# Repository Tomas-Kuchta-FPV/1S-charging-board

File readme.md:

# 1S charging board
> A compact adapter board that lets standard RC chargers safely charge 1S batteries.

It allows you to charge up to six 1s batteries on a universal RC charger.  
Some chargers can display series resistance and capacity. So you know the conditions of the cells.  
Connectors like **BT2.0/A30** and **XT30** are suported. And with an adapter, you can charge **18650** batteries.  

## Photos
### Main PCB

### XT30 to 18650

## Motivation
I have a great RC charger (ISDT D1), and it measures internal resistance and capacity, which is awesome!  
There are a lot of 18650 cells of unknown condition lying in my workshop. I would like to know if they are still good or if they belong in the trash.  
Also, I love RC hobby. So why not use a universal both RC charger for RC and maker stuff?  
That's why there is a main PCB with XT30 and BT 2.0 connectors. And an extension board for 18650.

### Design constraints
- It should work with these battery types and connctors:
    - Modular design with BT2.0 on top and XT30 on the sides for modules.
    - XT30 - Main board
    - BT2.0 / A30 Main board
    - PH2.0 - future adapters if I need them
    - 18650 batteries - XT30 to 18650
- easy to use
- A fuse - 2A Polyfuze
- 6S MAX

## BOM
| Item                       | Qty | Price | Link                                                  |
| :------------------------- | :-- | :---- | :---------------------------------------------------- |
|                            |     |       |                                                       |
| BT2.0M                     | 6   | 7.15  | https://www.aliexpress.com/item/1005004465425088.html |
| 2A Polyfuse                | 1   | 0.51  | https://www.lcsc.com/product-detail/C960026.html      |
| XT60 - Power Input         | 1   | 0.59  | https://www.lcsc.com/product-detail/C98732.html       |
| 1x7P -  Balance input      | 1   | 0.54  | https://www.lcsc.com/product-detail/C144398.html      |
| 2x07 PinHeader             | 1   | 1.4   | https://www.lcsc.com/product-detail/C2897408.html     |
| XT30M                      | 6   | 1.72  | https://www.lcsc.com/product-detail/C431092.html      |
|                            |     |       |                                                       |
| XT30F                      | 6   | 1.92  | https://www.lcsc.com/product-detail/C2913282.html     |
| 18650 holder               | 6   | 7.52  | https://www.lcsc.com/product-detail/C2988620.html     |
| LCSC Shipping              |     | 11.2  |                                                       |
| PCB fabrication + shipping | 2   | 21.9  |                                                       |
|                            |     | 54.45 |                                                       |

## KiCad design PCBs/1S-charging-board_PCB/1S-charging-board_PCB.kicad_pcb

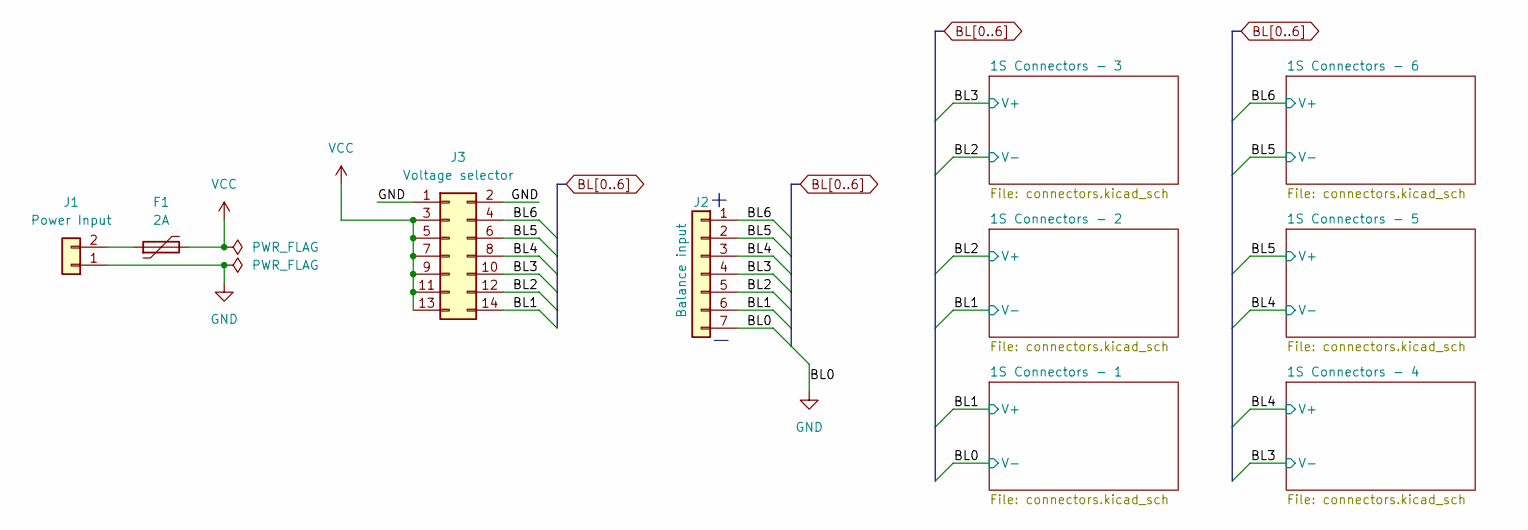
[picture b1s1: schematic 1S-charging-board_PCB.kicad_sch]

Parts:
F1: 2A; Fuse_1812_4532Metric_Pad1.30x3.40mm_HandSolder; LCSC C960026
J1: Power Input; AMASS_XT60PW-M_1x02_P7.20mm_Horizontal; LCSC C98732
J2: Balance input; JST_XH_B7B-XH-A_1x07_P2.50mm_Vertical; LCSC C144398
J3: Voltage selector; PinHeader_2x07_P2.54mm_Vertical; LCSC C2897408

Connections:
BL1: J2.6, J3.14; also elsewhere on the board
BL2: J2.5, J3.12; also elsewhere on the board
BL3: J2.4, J3.10; also elsewhere on the board
BL4: J2.3, J3.8; also elsewhere on the board
BL5: J2.2, J3.6; also elsewhere on the board
BL6: J2.1, J3.4; also elsewhere on the board
GND: J1.1, J2.7, J3.1, J3.2; also elsewhere on the board
unnamed: F1.1, J1.2
VCC: F1.2, J3.3, J3.5, J3.7, J3.9, J3.11, J3.13

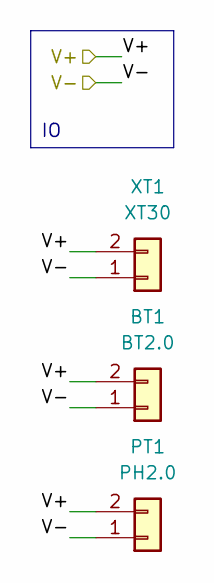
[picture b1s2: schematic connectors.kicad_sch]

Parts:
BT1: BT2.0; BT20
PT1: PH2.0; JST_PH_B2B-PH-K_1x02_P2.00mm_Vertical; LCSC C131337
XT1: XT30; AMASS_XT30PW-M_1x02_P2.50mm_Horizontal; LCSC C431092

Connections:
BL1: BT1.2, XT1.2; also elsewhere on the board
GND: BT1.1, XT1.1; also elsewhere on the board

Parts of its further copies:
BT2, BT3, BT4, BT5, BT6: BT2.0; BT20
XT2, XT3, XT4, XT5, XT6: XT30; AMASS_XT30PW-M_1x02_P2.50mm_Horizontal; LCSC C431092

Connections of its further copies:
BL1: BT2.1, XT2.1; also elsewhere on the board
BL2: BT2.2, BT3.1, XT2.2, XT3.1; also elsewhere on the board
BL3: BT3.2, BT4.1, XT3.2, XT4.1; also elsewhere on the board
BL4: BT4.2, BT5.1, XT4.2, XT5.1; also elsewhere on the board
BL5: BT5.2, BT6.1, XT5.2, XT6.1; also elsewhere on the board
BL6: BT6.2, XT6.2; also elsewhere on the board

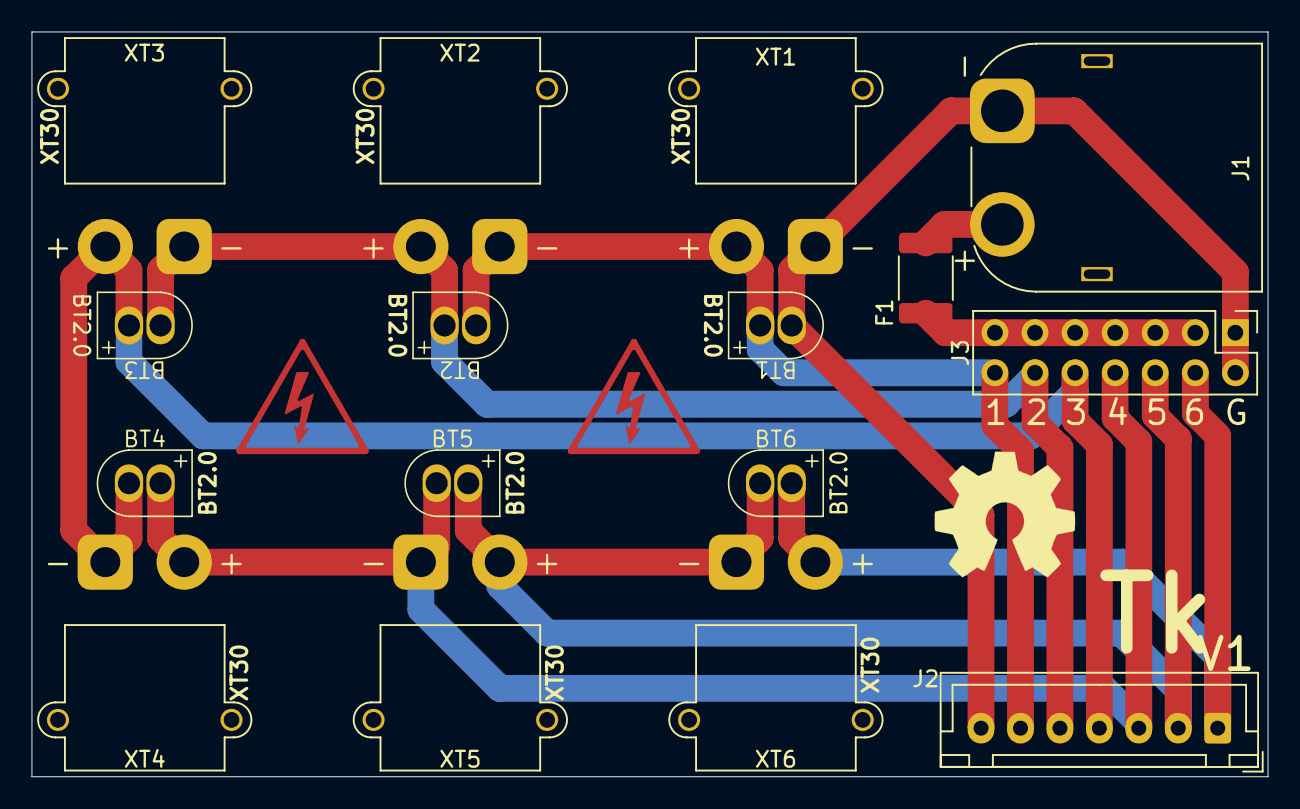
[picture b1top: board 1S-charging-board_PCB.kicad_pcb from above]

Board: 2 copper layers, 78.3 x 47.2 mm, 16 parts (0 on the bottom side), 9 nets.

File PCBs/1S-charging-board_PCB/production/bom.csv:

Designator,Footprint,Quantity,Value,LCSC Part #
"BT1, BT2, BT3, BT4, BT5, BT6",BT20,6,BT2.0,-
F1,1812,1,2A,C960026
J1,AMASS_XT60PW-M_1x02_P7.20mm_Horizontal,1,Power Input,C98732
J2,JST_XH_B7B-XH-A_1x07_P2.50mm_Vertical,1,Balance input,C144398
J3,PinHeader_2x07_P2.54mm_Vertical,1,Voltage selector,C2897408
"XT1, XT2, XT3, XT4, XT5, XT6",AMASS_XT30PW-M_1x02_P2.50mm_Horizontal,6,XT30,C431092

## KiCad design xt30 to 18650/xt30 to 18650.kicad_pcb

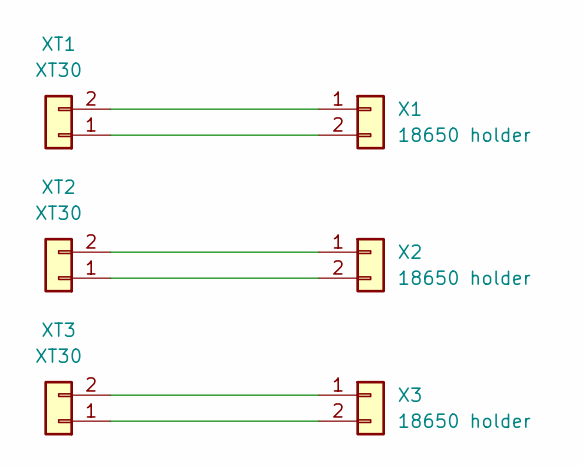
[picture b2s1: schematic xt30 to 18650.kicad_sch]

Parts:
X1, X2, X3: 18650 holder; BatteryHolder_Keystone_1042_1x18650; LCSC C2988620
XT1, XT2, XT3: XT30; AMASS_XT30PW-F_1x02_P2.50mm_Horizontal; LCSC C2913282

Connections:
unnamed: X1.1, XT1.2
unnamed: X1.2, XT1.1
unnamed: X2.1, XT2.2
unnamed: X2.2, XT2.1
unnamed: X3.1, XT3.2
unnamed: X3.2, XT3.1

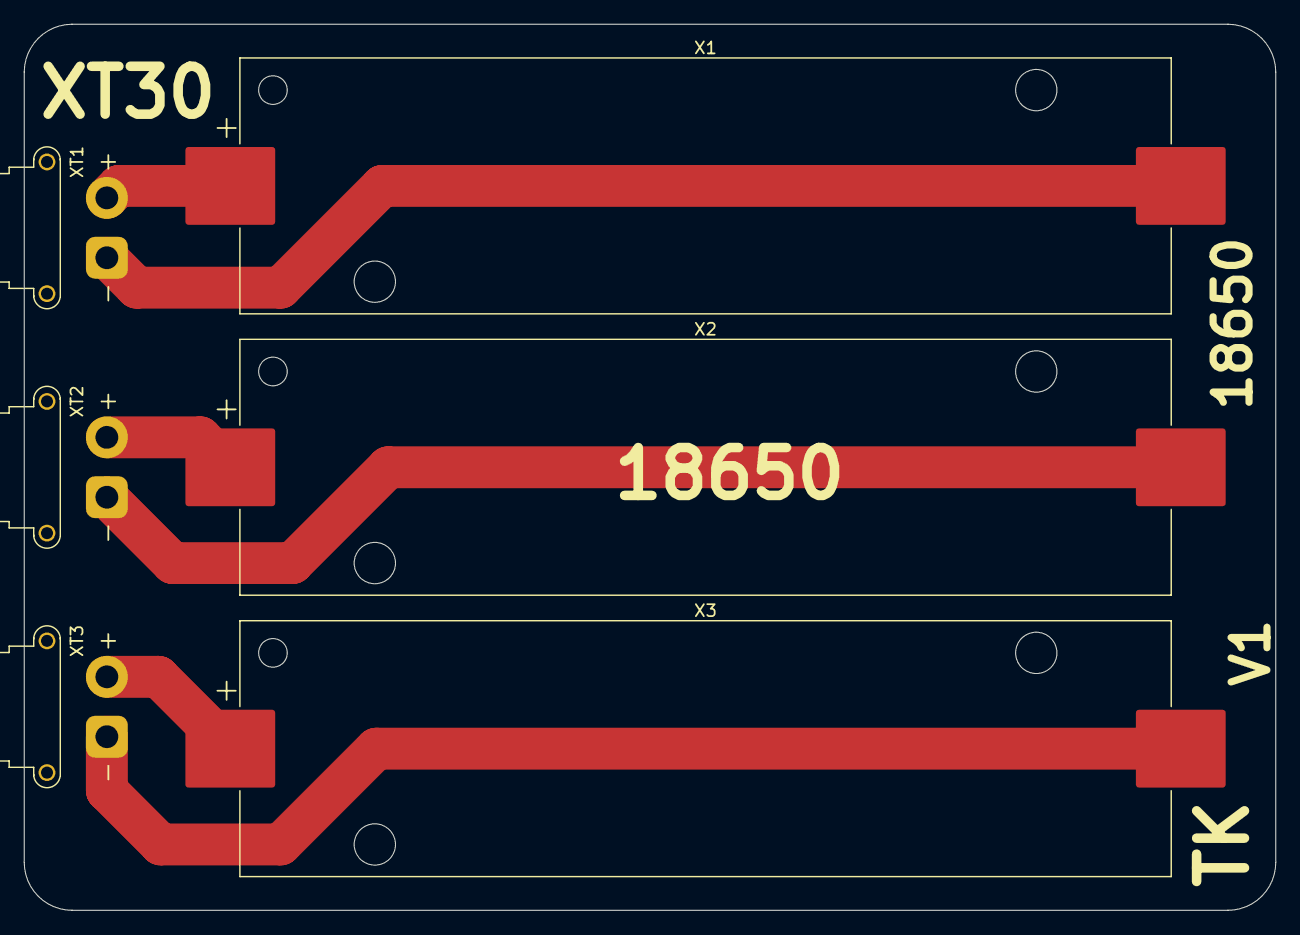
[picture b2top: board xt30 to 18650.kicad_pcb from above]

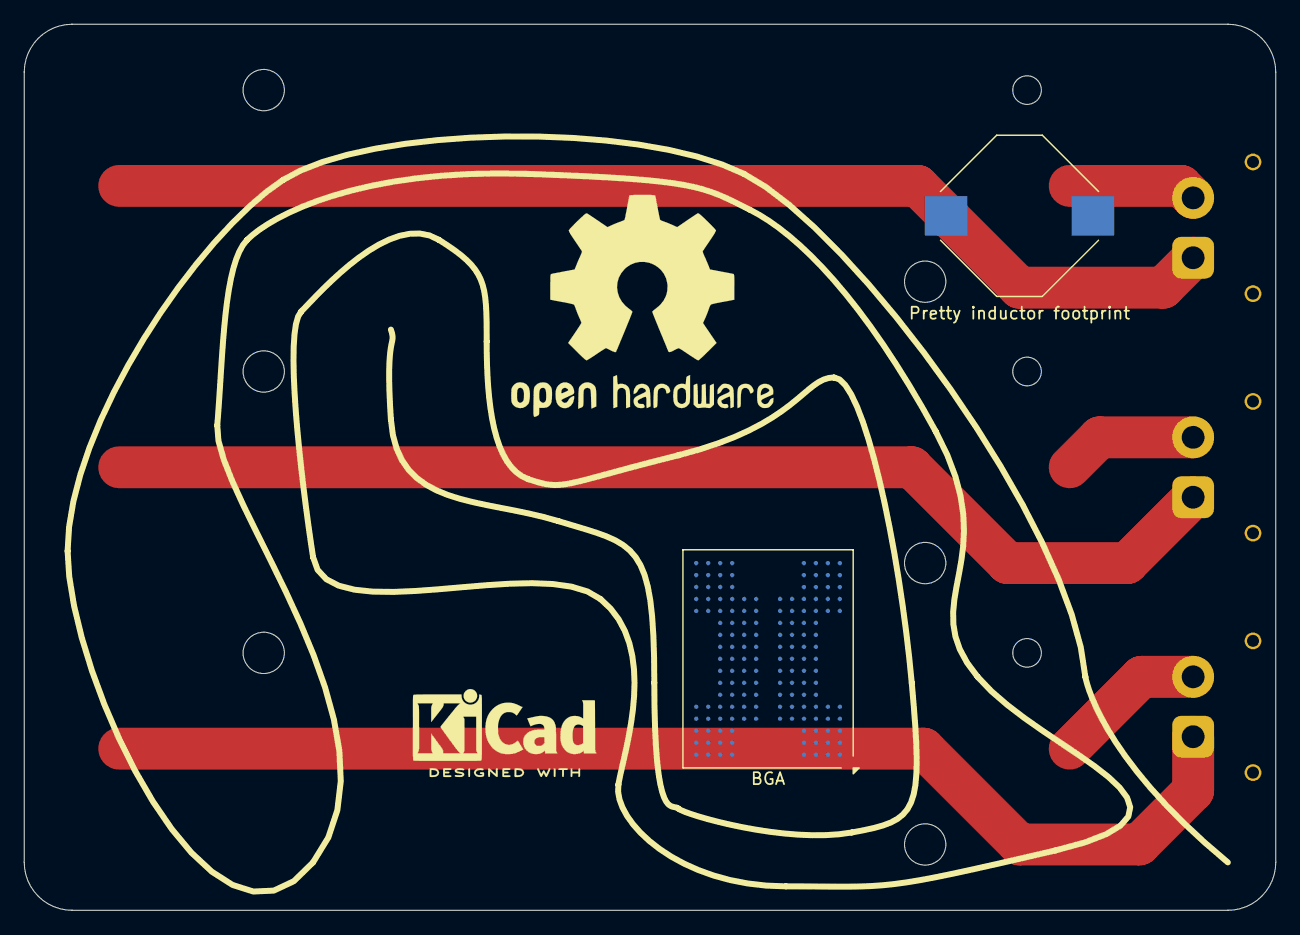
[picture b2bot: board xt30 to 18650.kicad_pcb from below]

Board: 2 copper layers, 104.5 x 74.0 mm, 8 parts (2 on the bottom side), 6 nets.

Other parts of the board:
BGA: BGA-152_14x18mm_Layout13x17_P1mm
Pretty inductor footprint: L_Sagami_CER1257B

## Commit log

2025-11-19 Added PCB with schematic pretty much finished
2025-11-19 Added courtyard.
2025-11-25 Finished the 1s charging board.
2025-11-28 Made a XT30 to 18650 board.
2025-11-28 prep for submiting
2025-11-28 PH20
2025-11-28 added BOM and other CSV stuff
2025-11-29 Finalized readme and checked grammar.
2025-11-29 Forgor shipping on aliexpress
